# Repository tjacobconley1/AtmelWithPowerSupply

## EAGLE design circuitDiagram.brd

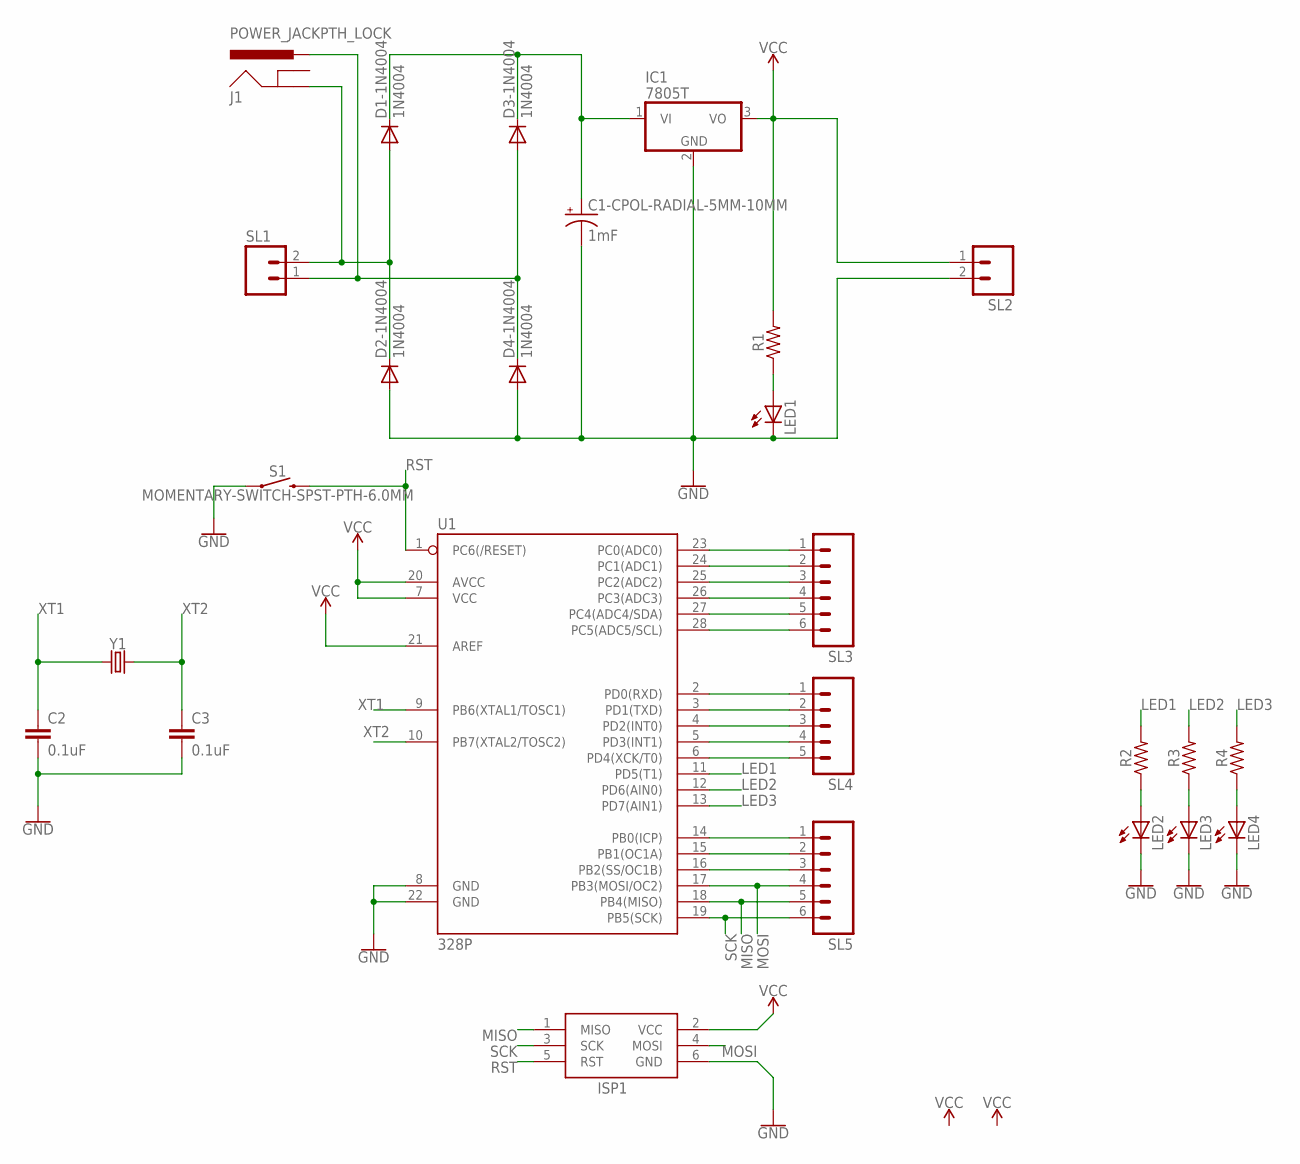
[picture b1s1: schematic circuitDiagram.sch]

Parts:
C1-CPOL-RADIAL-5MM-10MM: 1mF; CPOL-RADIAL-5MM-10MM
C2, C3: 0.1uF; CAP-PTH-SMALL-KIT
D1-1N4004, D2-1N4004, D3-1N4004, D4-1N4004: 1N4004; DO41-10
IC1: 7805T; TO220H
ISP1: AVRISP-6; AVRISP
J1: POWER_JACKPTH_LOCK; POWER_JACK_PTH_LOCK
LED1, LED2, LED3, LED4: LED3MM
R1, R2, R3, R4: AXIAL-0.3
S1: MOMENTARY-SWITCH-SPST-PTH-6.0MM; TACTILE_SWITCH_PTH_6.0MM
SL1, SL2: M02; 02P
SL3, SL5: M06; 06P
SL4: M05; 05P
U1: 328P; DIP28
Y1: CRYSTALPTH-HC49US; HC49US

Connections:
GND: C1-CPOL-RADIAL-5MM-10MM.-, C2.2, C3.2, D2-1N4004.A, D4-1N4004.A, IC1.2 (GND), ISP1.6 (GND), LED1.K (C), LED2.K (C), LED3.K (C), LED4.K (C), S1.1, SL2.2, U1.8 (GND), U1.22 (GND)
LED1: R2.P$2 (2), U1.11 (PD5(T1))
LED2: R3.P$2 (2), U1.12 (PD6(AIN0))
LED3: R4.P$2 (2), U1.13 (PD7(AIN1))
MISO: ISP1.1 (MISO), SL5.5, U1.18 (PB4(MISO))
MOSI: ISP1.4 (MOSI), SL5.4, U1.17 (PB3(MOSI/OC2))
unnamed: LED1.A, R1.P$1 (1)
unnamed: D1-1N4004.A, D2-1N4004.C, J1.GND, SL1.2
unnamed: C1-CPOL-RADIAL-5MM-10MM.+, D1-1N4004.C, D3-1N4004.C, IC1.1 (VI)
unnamed: D3-1N4004.A, D4-1N4004.C, J1.PWR, SL1.1
unnamed: LED2.A, R2.P$1 (1)
unnamed: LED3.A, R3.P$1 (1)
unnamed: LED4.A, R4.P$1 (1)
unnamed: SL3.1, U1.23 (PC0(ADC0))
unnamed: SL3.2, U1.24 (PC1(ADC1))
unnamed: SL3.3, U1.25 (PC2(ADC2))
unnamed: SL3.4, U1.26 (PC3(ADC3))
unnamed: SL3.5, U1.27 (PC4(ADC4/SDA))
unnamed: SL3.6, U1.28 (PC5(ADC5/SCL))
unnamed: SL4.1, U1.2 (PD0(RXD))
unnamed: SL4.2, U1.3 (PD1(TXD))
unnamed: SL4.3, U1.4 (PD2(INT0))
unnamed: SL4.4, U1.5 (PD3(INT1))
unnamed: SL4.5, U1.6 (PD4(XCK/T0))
unnamed: SL5.1, U1.14 (PB0(ICP))
unnamed: SL5.2, U1.15 (PB1(OC1A))
unnamed: SL5.3, U1.16 (PB2(SS/OC1B))
RST: ISP1.5 (RST), S1.3 (2), U1.1 (PC6(/RESET))
SCK: ISP1.3 (SCK), SL5.6, U1.19 (PB5(SCK))
VCC: IC1.3 (VO), ISP1.2 (VCC), R1.P$2 (2), SL2.1, U1.7 (VCC), U1.20 (AVCC), U1.21 (AREF)
XT1: C2.1, U1.9 (PB6(XTAL1/TOSC1)), Y1.1
XT2: C3.1, U1.10 (PB7(XTAL2/TOSC2)), Y1.2

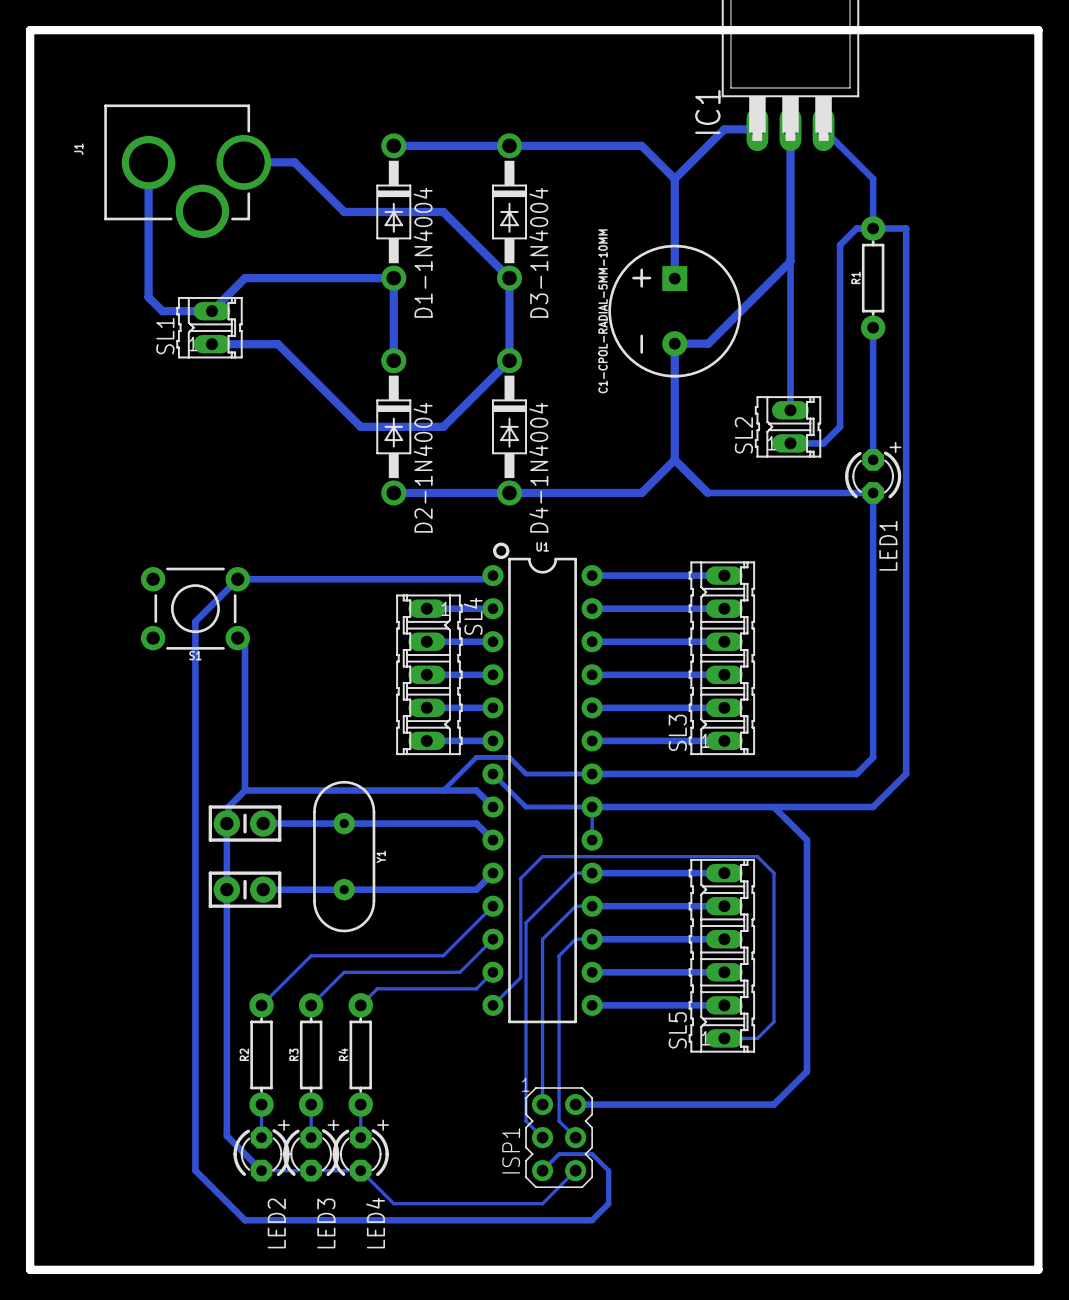
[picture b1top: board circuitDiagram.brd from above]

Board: 2 copper layers, 77.5 x 95.2 mm, 26 parts (0 on the bottom side), 32 nets.

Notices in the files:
parts and their libraries:
SparkFun-Capacitors: Licensing: Creative Commons ShareAlike 4.0 International - https://creativecommons.org/licenses/by-sa/4.0
